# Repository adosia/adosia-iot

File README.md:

# The Adosia IoT Platform - [adosia.com](https://adosia.com)

The **Adosia IoT Platform** is a free cloud based tool paired with an open hardware initiative that enables anyone to create, customize, deploy and manage custom WiFi control systems using supported open IoT WiFi hardware.

The next phase of development for the Adosia IoT Platform will leverage cryptocurrency to enable Adosia users with a peer-to-peer marketplace to sell/license their IoT creations to other Adosia users.

**Learn More About the Adosia IoT Platform - see the [Adosia Learn Page](https://adosia.com/faq.php)**

You can support Adosia open hardware development by sending any amount of ADA to the following Cardano address:
**addr1qx0w683ua2hua30jhan3xfn5f473pjgh4vgxpx7mnuwfxddyah4yv7wh5dktyxs4cf7gf72pqa39twrp3qs56v0e6y4qupjq4t**

# Dashboard View - Connected IoT Devices

# How to Connect IoT Hardware to the Adosia IoT Platform

**1. Sign Up FREE for the [Adosia IoT Platform](https://adosia.com)**

**2. Obtain compatible IoT hardware pre-flashed with the latest Adosia binary by either:**

  - purchasing a WEMOS WiFi baseboard pre-flashed with the Adosia binary (along with optional [Adosia SPACE IO board](https://adosia.io/product/adosia-iot-space-io-board-shield/)) from the [Adosia IoT Store](https://adosia.io)
 
  - or you can use the popular Arduino IDE to download by latest Adosia binary by flashing your own WEMOS WiFi baseboard with Adosia's open source [phoenix connect script](https://github.com/adosia/adosia-iot/tree/master/adosia_phoenix)

**3. Use a mobile device to connect your IoT hardware to the Adosia IoT Platform (see [Adosia Learn Page](https://adosia.com/faq.php))**

Compatible open hardware boards flashed using Adosia's open source [phoenix connect script](https://github.com/adosia/adosia-iot/tree/master/adosia_phoenix) and the Arduino IDE will automatically connect to Adosia servers to download the latest Adosia binary.

The schematics and layout files for Adosia's open hardware SPACE v2.2 IO board (compatible with WEMOS D1 R2 WiFi baseboard) can be found [here](https://github.com/adosia/adosia-iot/tree/master/SPACE_v2.2/hardware/IO_BOARD_WEMOS_D1R2)

Adosia will publish manufacturing schematics and layout files for an IO board compatible with the WEMOS D1 Mini baseboard in the near future.

# Setting Up an IoT Device Profile

# ADO Token Allocations for Early Adosia IoT Platform Adopters

Prior to the future release of the ADO smart contract on the Cardano blockchain, a random amount of ADO tokens will be tentatively allocated to a respective
Adosia IoT Platform user's account whenever that user first connects (and activates) any Adosia-supported open hardware IoT device to the Adosia IoT Platform.

Once the Adosia platform confirms newly connected IoT hardware to be a legitimate IoT device (ruling out bot connections, platform manipulation, etc.),
the respective tentative token allocation will be secured to the connecting user's account with the Adosia IoT Platform. All token allocations secured prior to the production release
of the ADO smart contract (following Cardano smart contract availability) will become transferable to the respective user's Cardano wallet address upon the release of the ADO smart contract.

The Adosia IoT Platform supports ESP8266-based WiFi baseboards which currently include the WEMOS D1 R2 and WEMOS D1 Mini WiFi baseboards,
and does not require users to purchase hardware from (or manufactured by) Adosia.  This enables anyone in the world the ability to begin using and creating with the Adosia IoT Platform for free.

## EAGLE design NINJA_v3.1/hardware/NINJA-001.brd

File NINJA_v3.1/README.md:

# Adosia NINJA Capacitive Analog Soil Moisture Sensor

The Adosia NINJA Capacitive Analog Soil Moisture Sensor design is part of Adosia's open hardware IO platform initiative to enable anyone to easily create a variety of custom WiFi control systems using the **Adosia IoT Platform**.

The Adosia NINJA sensor is designed to be compatible with popular open hardware microcontroller boards including **Arduino**, **ESP8266**, **Raspberry Pi**, **Adosia IoT** and more.

You can support Adosia open hardware development by sending any amount of ADA to the following Cardano address:
**DdzFFzCqrhssyL8yoWBsM1NbhozhNu7yZ2vM355AauDt5MrC3kmzaJC8iwE8VC6MB4QmJ2p9diiGaM5wFYruE5gtsizFV4SyfQjUjyDX**

# Adosia NINJA Features:

- corrosion resistant by design

- capacitive sense technology for longer field life

- input voltage: 3.3 ~ 5.0 VDC

- output voltage: 0 ~ 3.0 VDC

- footprint open for custom header pin / connector

- dimension: 98mm * 22mm (3.86in x 0.866in)

# Applications:

- automate watering for gardening / hydroponics / aquaponics

- self-watering pots and planters

- personal cultivation setups and feeder control systems

- moisture level monitoring

- nursery and tree care

- IoT data applications

Navigate the hardware subdirectory to find the schematics, layout file, gerbers and BOM which can be used to manufacture this board

[Buy Adosia IoT Hardware](https://adosia.io)

*NINJA was inspired by the open hardware capacitive soil moisture sensor by DFRobot

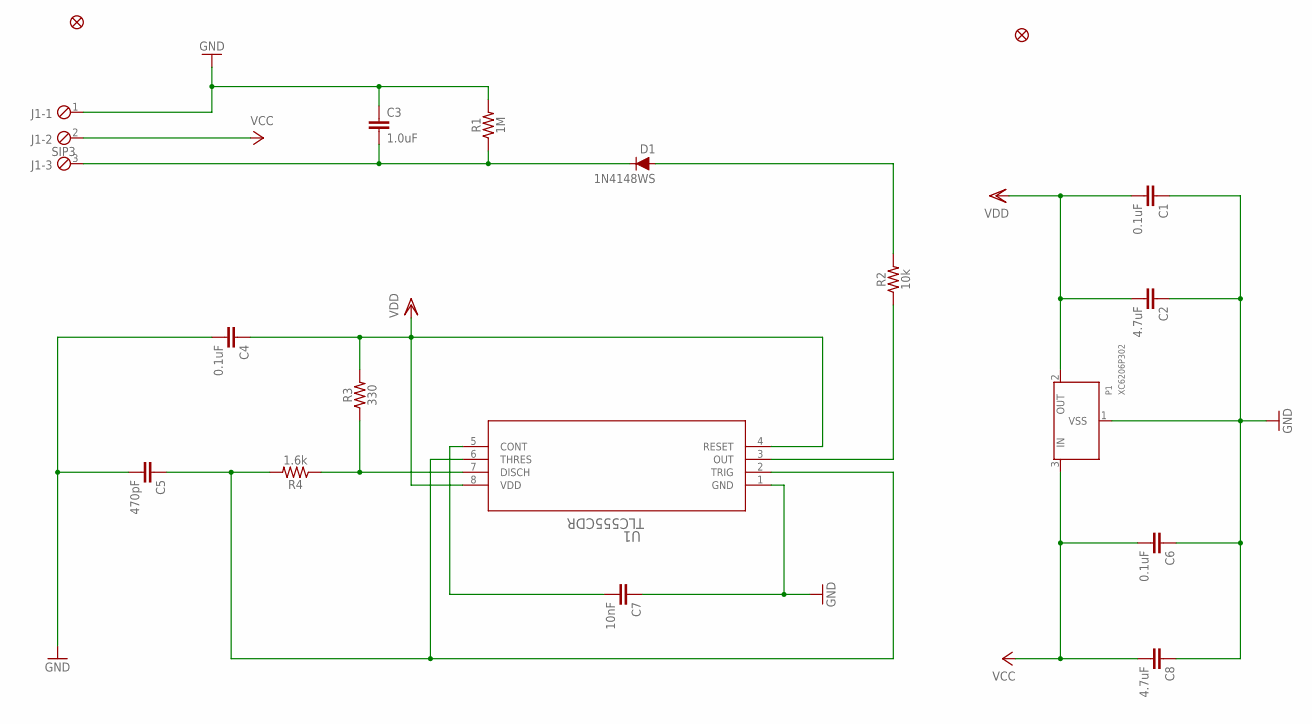
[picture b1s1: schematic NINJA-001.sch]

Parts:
C1, C4, C6: 0.1uF; 0603
C2, C8: 4.7uF; 0603
C3: 1.0uF; 0603
C5: 470pF; 0603
C7: 10nF; 0603
D1: 1N4148WS; SOD-323
FD1, FD2: FIDUCIAL1X2; FIDUCIAL-1X2
J1: SIP3; 3POL254
P1: XC6206P302; XC6206_SOT-23
R1: 1M; 0603
R2: 10k; 0603
R3: 330; 0603
R4: 1.6k; 0603
U1: TLC555CDR; D8

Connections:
A: C3.2, D1.C, J1.3, R1.1
GND: C1.1, C2.1, C3.1, C4.2, C5.2, C6.1, C7.1, C8.1, J1.1, P1.1 (VSS), R1.2, U1.1 (GND)
unnamed: R2.1, U1.3 (OUT)
unnamed: D1.A, R2.2
unnamed: R3.1, R4.1, U1.7 (DISCH)
unnamed: C7.2, U1.5 (CONT)
unnamed: C5.1, R4.2, U1.2 (TRIG), U1.6 (THRES)
VCC: C6.2, C8.2, J1.2, P1.3 (IN)
VDD: C1.2, C2.2, C4.1, P1.2 (OUT), R3.2, U1.4 (RESET), U1.8 (VDD)

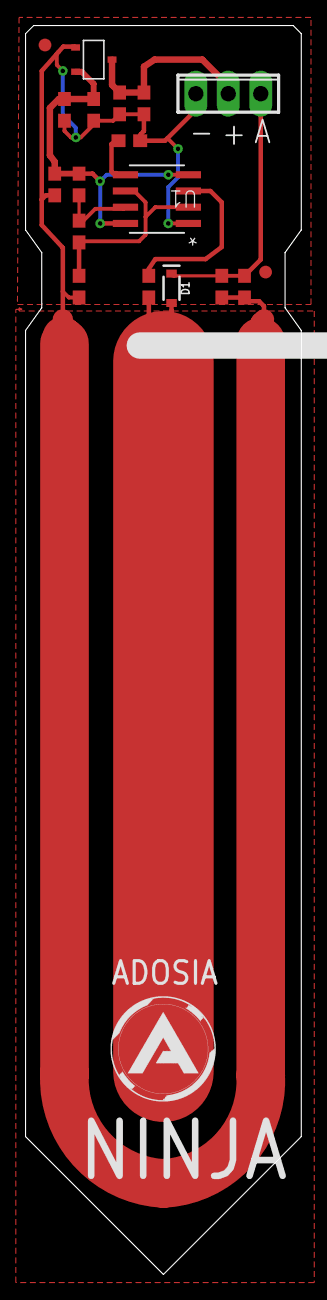
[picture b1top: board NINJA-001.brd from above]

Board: 2 copper layers, 21.6 x 97.8 mm, 18 parts (0 on the bottom side), 9 nets.

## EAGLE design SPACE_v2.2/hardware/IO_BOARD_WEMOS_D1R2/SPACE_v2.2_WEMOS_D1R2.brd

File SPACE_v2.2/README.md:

# Adosia SPACE IO Shield - [Buy Adosia IoT Hardware](https://adosia.io)

Adosia SPACE IO boards are part of Adosia's open hardware IO platform initiative to enable anyone to easily create a variety of custom WiFi control systems using the **Adosia IoT Platform**.

The SPACE IO shield is designed to be pin compatible with the popular open hardware **Arduino Uno R3** and **WEMOS D1 R2 WiFi** controller boards.

Use the Arduino IDE and Adosia's open source [phoenix connect script](https://github.com/adosia/adosia-iot/tree/master/adosia_phoenix) to connect your ESP8266-based SPACE IO hardware
(compatible with WEMOS D1 R2 or WEMOS D1 Mini) to the Adosia IoT Platform which automatically downloads the latest Adosia binary.

# SPACE for WEMOS D1 R2

*SPACE for the WEMOS D1 Mini coming soon*

# Adosia SPACE IO Board Features (WEMOS D1 R2):

- x2 diode-protected transistor switch channels to safely drive pumps or solenoids

- x2 digital IO pins tied to onboard 4.7kΩ pullups (water level sensor switch or temperature sensor)

- x2 digital IO pins (relays, motion detectors, push buttons, tilt sensors, vibration sensors, etc)

- x1 analog port

- bright onboard RGB LED

- breakout voltage supply headers providing 2x GND, 2x 3.3v, 2x 5v and 2x Vin

# Applications:

- custom WiFi control systems / home automation

- gardening / hydroponics / aquaponics

- motion detect sentry and alarm applications

- personal cultivation feeder control systems

- refill water reservoir on detecting low water

- custom tamper alarms

- digital lock applications

- temperature sensor triggered fan control

- lighting / appliance power control

- wide array of WiFi / IoT / relay applications

*recommended supply voltage for WEMOS D1 R2 with the Adosia IoT Platform: Vin = 12V*

*transistor/diode switch channels can drive up to 450mA at supply voltage Vin*

*relays trigger on programmatic LOW*

Navigate the hardware subdirectory to find the schematics and layout file that can be used to manufacture this board

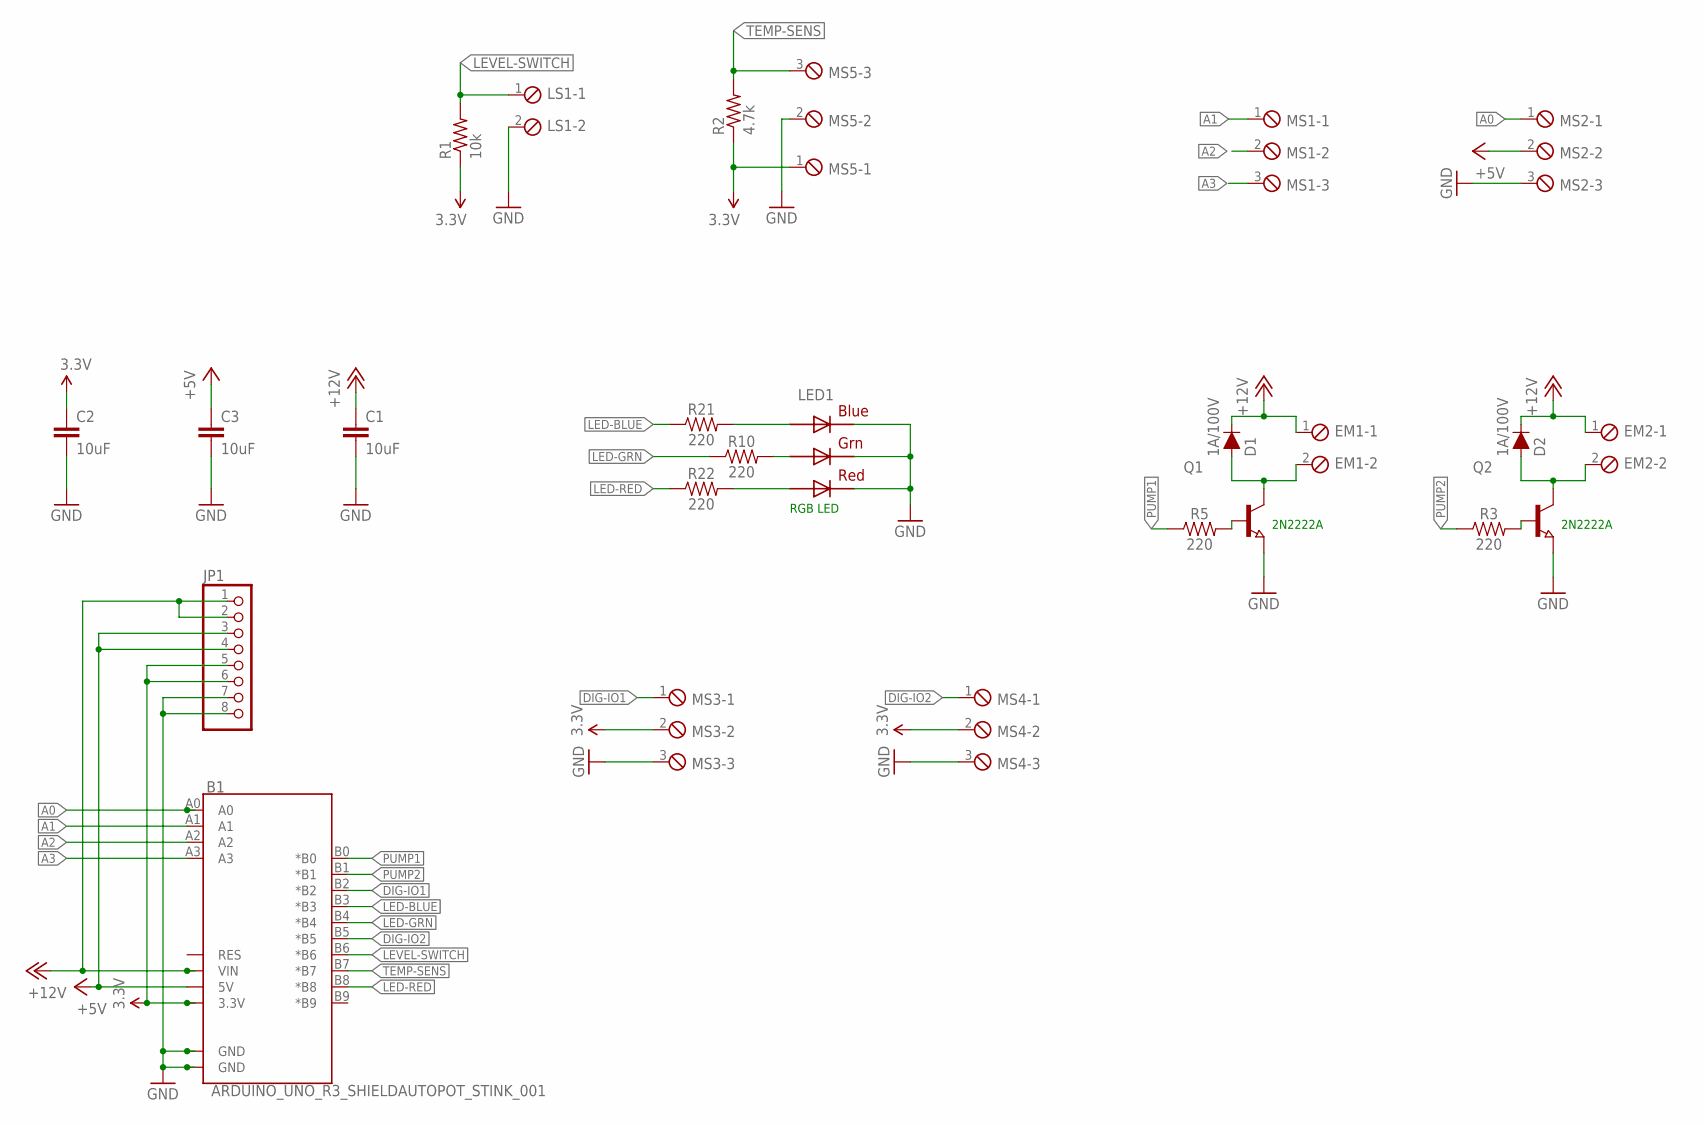
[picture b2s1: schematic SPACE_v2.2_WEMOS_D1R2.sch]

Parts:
B1: ARDUINO_UNO_R3_SHIELDAUTOPOT_STINK_001; UNO_R3_SHIELD_LOCK
C1, C2, C3: 10uF; 0603-CAP@1
D1, D2: 1A/100V; SOD-323
EM1, EM2: MPT2; 2POL254
JP1: PINHD-1X8/90; 1X08/90
LED1: RGBLED5050
LS1: MPT2; 2POL254
MS1, MS2, MS3, MS4, MS5: MPT3; 3POL254
Q1, Q2: NPN-TRANSISTOR_SOT23; SOT23
R1: 10k; M1206
R2: 4.7k; M1206
R3, R5, R10, R21, R22: 220; 0603

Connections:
3.3V: B1.3.3V, C2.1, JP1.5, JP1.6, MS3.2, MS4.2, MS5.1, R1.1, R2.1
+5V: B1.5V, C3.1, JP1.3, JP1.4, MS2.2
+12V: B1.VIN, C1.1, D1.C, D2.C, EM1.1, EM2.1, JP1.1, JP1.2
A0: B1.A0, MS2.1
A1: B1.A1, MS1.1
A2: B1.A2, MS1.2
A3: B1.A3, MS1.3
DIG-IO1: B1.B2 (*B2), MS3.1
DIG-IO2: B1.B5 (*B5), MS4.1
GND: B1.GND@0 (GND), B1.GND@1 (GND), C1.2, C2.2, C3.2, JP1.7, JP1.8, LED1.4 (BLUE_C), LED1.5 (RED_C), LED1.6 (GREEN_C), LS1.2, MS2.3, MS3.3, MS4.3, MS5.2, Q1.2 (E), Q2.2 (E)
LED-BLUE: B1.B3 (*B3), R21.1
LED-GRN: B1.B4 (*B4), R10.1
LED-RED: B1.B8 (*B8), R22.1
LEVEL-SWITCH: B1.B6 (*B6), LS1.1, R1.2
unnamed: LED1.3 (BLUE_A), R21.2
unnamed: Q2.1 (B), R3.2
unnamed: Q1.1 (B), R5.2
unnamed: D2.A, EM2.2, Q2.3 (C)
unnamed: D1.A, EM1.2, Q1.3 (C)
unnamed: LED1.2 (RED_A), R22.2
unnamed: LED1.1 (GREEN_A), R10.2
PUMP1: B1.B0 (*B0), R5.1
PUMP2: B1.B1 (*B1), R3.1
TEMP-SENS: B1.B7 (*B7), MS5.3, R2.2

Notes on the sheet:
RGB LED
2N2222A

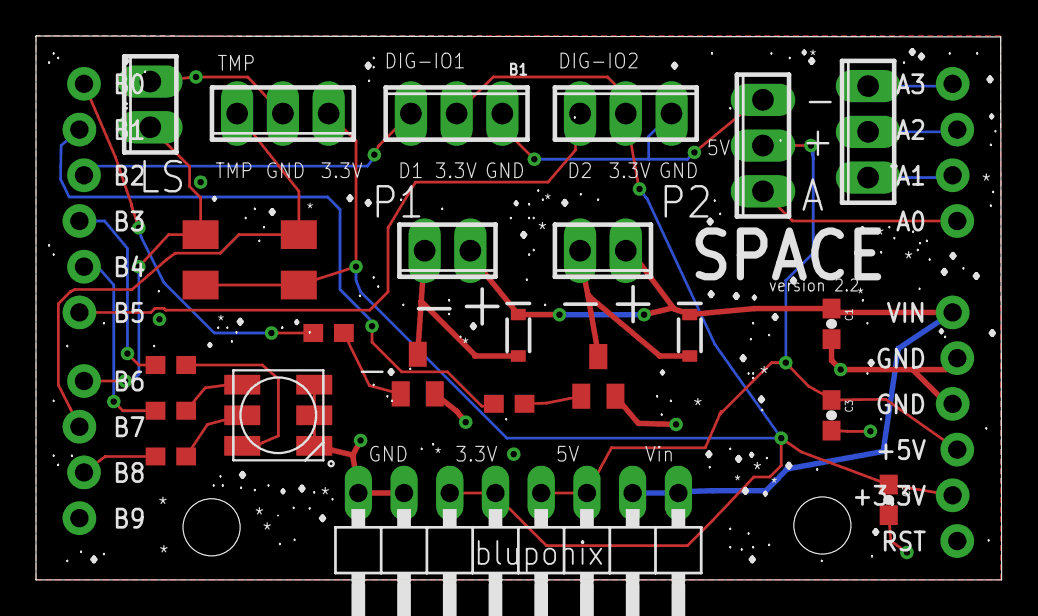
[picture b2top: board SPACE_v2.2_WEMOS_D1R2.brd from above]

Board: 2 copper layers, 53.6 x 30.2 mm, 25 parts (0 on the bottom side), 24 nets.

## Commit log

2019-09-03 arise phoenix
2019-09-03 add .gitignore
2019-09-03 .gitignore fix
2019-09-22 phoenix updates
2019-11-20 new space2.2 enclosures designed by Chris K.
2020-05-21 open up NINJA
2020-06-17 update readme ninja
2020-06-17 update readmes
2021-01-17 Create LICENSE
2021-01-17 Update LICENSE

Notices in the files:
parts and their libraries:
SparkFun-Capacitors: Licensing: Creative Commons ShareAlike 4.0 International - https://creativecommons.org/licenses/by-sa/4.0
SparkFun-Aesthetics: Licensing: CC v3.0 Share-Alike You are welcome to use this library for commercial purposes.
